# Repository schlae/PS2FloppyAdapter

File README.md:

# PS/2 Floppy Adapter

This PS/2 floppy adapter is designed to allow standard PC floppy drives to be
used in IBM PS/2 systems that have 40-pin edge connectors for their floppy
drive interfaces. This can be quite useful because many PS/2 floppy drives have failed due to leaking capacitors or mechanical problems, and can be difficult or impossible to repair.

Compatible models include

* IBM PS/2 Model 50 and 50Z
* IBM PS/2 Model 70

Here's what the adapter looks like when installed in a Model 50Z.

## Connector PC Board

There are several pieces to the design. First, there is a circuit board: the design files are here.

[Schematic](https://github.com/schlae/PS2FloppyAdapter/blob/master/PS2FloppyAdapter.pdf)

[Fab Files](https://github.com/schlae/PS2FloppyAdapter/blob/master/cam/PS2FloppyDaughterboardRevA.zip)

The bill of materials is as follows:

| Designator | Quantity | Description                  |
| ---------  | -------- | ---------------------------- |
|        J2  |        1 | 34-pin 0.1" breakaway header |
|      R1-R5 |        5 | 1K ohm resistors, 0603       |

Note that R1-R5 can be either 1% or 5% since the exact value is not critical.

J3 provides power to the PC floppy drive. One way to build it is to cut off
a 0.1" power header from an old PC power supply, Y splitter, or similar
adapter, and then solder the wires to the appropriate connections on the
adapter board. Black to ground, red to +5V, and yellow to +12V.

You'll also need a short length of 34-pin ribbon cable with a male IDC connector crimped onto each end. This connects the adapter board to the floppy drive.

## Mechanical Parts

Several parts mechanically adapt the standard PC floppy drive to fit in the
PS/2. Each of them can be printed on a commodity FDM 3D printer.

[Drive Sled](https://github.com/schlae/PS2FloppyAdapter/blob/master/mech/PS2_50_floppy_sled_15F7502.STL) - This is compatible with IBM FRU 15F7502. 

[Plugboard](https://github.com/schlae/PS2FloppyAdapter/blob/master/mech/PS2_50_floppy_plugboard.STL) - The plugboard sits between the floppy drive and the connector PC board, holding it at just the right angle.

[Eject button (Sony MPF920)](https://github.com/schlae/PS2FloppyAdapter/blob/master/mech/PS2_50_floppy_button_sony_mpf920.STL) - Eject button for the Sony MPF920 floppy drive

[Eject button (Teac FD235HF)](https://github.com/schlae/PS2FloppyAdapter/blob/master/mech/PS2_50_floppy_button_teac_fd235HF.STL) - Eject button for the Teac FD235HF floppy drive

The STL files are oriented in the optimal orientations for printing. The sled has some overhangs and will require supports to be added in order to print correctly.

* Two M3-0.5mm, 5mm long self tapping screws. These attach the PCB to the plugboard.

* Four M3-0.5mm, 10mm long machine screws. These attach the floppy drive to the sled.

## Assembly

Remove the old floppy drive bezel. The exact way to do this varies depending on the drive, but typically there are plastic tabs on the sides that clip into the drive. On some drives you may have to remove the metal lid to get at them.

Remove the old eject button from the floppy drive. The Sony drive button simply slides up. You might have to rock it back and forth a bit. The Teac drive button is harder to remove; if you get in with a dental pick or screwdriver, pull up the plastic catch and the button should slide straight out.

Install the new eject button just like you removed the old one but in reverse. If it refuses to go in, don't force it. There are some fairly detailed features that may require cleanup with a sharp knife in order for it to fit.

Before installing the drive on the sled, take the sled and heat the plastic locking tab in the front with a hair dryer or heat gun (low heat) and bend it down. It needs to bend down far enough to engage with a slot in the PS/2 chassis which locks it in place when it is installed.

Then, using the 10mm machine screws, install the drive on the sled. The floppy drive slot should face the same direction as the locking tab on the sled.

Install the PC board on the plastic plugboard using the two self-tapping screws. You can temporarily tape it in place to figure out how long the 34-pin IDC cable and the drive power cable need to be.

Now slide the assembly into your PS/2 computer and plug the PC board into the slot at the back of the drive bay. The plugboard should rest on the top of the floppy drive. Make a mark so you know exactly where it should go. Then remove the assembly and glue the plugboard to the top of the floppy drive, right where you placed your mark. You can try using double-sided tape, but 3M VHB (Very High Bond) is probably the most secure.

I've found that the drive LED lines up fairly well with the LED window on the stock PS/2 drive bezel (IBM FRU 15F7534).

There is a variant of the drive bezel, FRU 62X0362, which has the LED above the drive slot, which won't work. You'll need to run a wire and hot glue the LED on top of the floppy drive or print a replacement bezel (see below).

## Optional Parts

I've also made a 3D-printable model of the PS/2 Model 50/50Z drive bezel if you want to install this drive as a second floppy drive, or if your machine was missing it.

This part is tricky to print and requires support structures. It is printed on the side so that the front panel texture will look reasonable, and also so that the plastic locking tabs will be sturdy. Use pliers and side cutters to remove the support structure, and be sure to wear safety glasses!

## Archive

Here is the old version of the floppy adapter PC board. This can be used to electrically connect a floppy drive to the IBM 40-pin connector used on some additional models, such as the Model 60 and 80. There is no mechanical mounting design for these models yet.

[Fab Files](https://github.com/schlae/PS2FloppyAdapter/blob/master/cam/PS2FloppyAdapterRevA.zip)

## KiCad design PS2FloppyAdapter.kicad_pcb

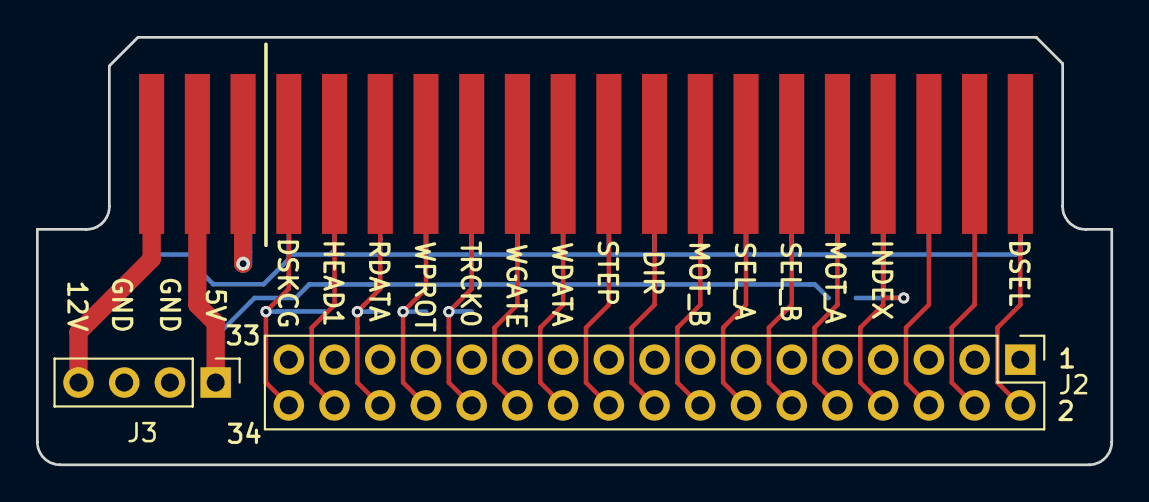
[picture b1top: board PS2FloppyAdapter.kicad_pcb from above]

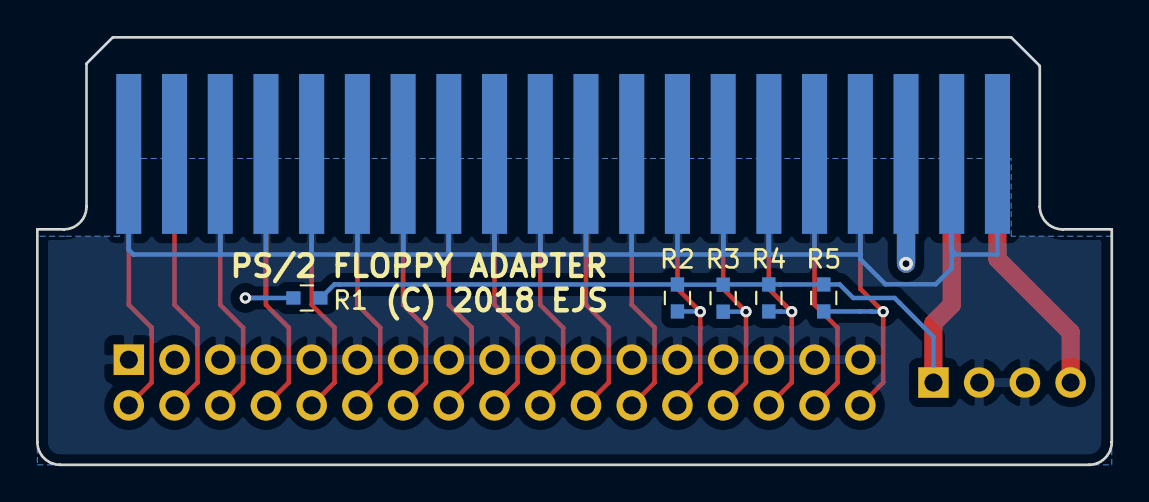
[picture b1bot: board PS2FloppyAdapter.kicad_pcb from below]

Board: 2 copper layers, 59.7 x 23.7 mm, 8 parts (5 on the bottom side), 21 nets.

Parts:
J1: Conn_02x20_Odd_Even; EDGE_FLOPPY40
J2: Conn_02x17_Odd_Even; Pin_Header_Straight_2x17_Pitch2.54mm
J3: Conn_01x04; Pin_Header_Straight_1x04_Pitch2.54mm
R1, R2, R3, R4, R5: 1K; RESC1608X55

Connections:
+5V: J1.38, J3.1, R1.1, R2.1, R3.1, R4.1, R5.1
+12V: J1.40, J3.4
/DIR: J1.18, J2.18
/DISKCHG: J1.34, J2.34, R5.2
/DSEL_A: J1.14, J2.14
/DSEL_B: J1.12, J2.12
/ENWRITE: J1.24, J2.24
/HDSEL: J1.2, J2.2
/HEAD1SEL: J1.32, J2.32
/INDEX: J1.8, J2.8, R1.2
/MOTEN_A: J1.10, J2.10
/MOTEN_B: J1.16, J2.16
/RDATA: J1.30, J2.30, R4.2
/RES1: J1.4, J2.4
/RES2: J1.6, J2.6
/STEP: J1.20, J2.20
/TRACK0: J1.26, J2.26, R2.2
/WDATA: J1.22, J2.22
/WPROT: J1.28, J2.28, R3.2
GND: J1.1, J1.5, J1.7, J1.9, J1.11, J1.13, J1.15, J1.17, J1.19, J1.21, J1.23, J1.25, J1.27, J1.29, J1.31, J1.33, J1.37, J1.39, J2.1, J2.5, J2.7, J2.9, J2.11, J2.13, J2.15, J2.17, J2.19, J2.21, J2.23, J2.25, J2.27, J2.29, J2.31, J2.33, J3.2, J3.3
unnamed: J1.35, J1.36

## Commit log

2020-03-21 Initial empty commit
2020-03-21 Initial version
2020-03-21 Fab out
2020-03-21 Add readme, update design files
2020-12-29 Added new board and mechanical parts

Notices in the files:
PS2FloppyAdapter.kicad_pcb:
Copyright (C) 2020 Eric Schlaepfer
License. See https://creativecommons.org/licenses/by-sa/4.0
This work is licensed under a Creative Commons Attribution-ShareAlike 4.0 International
(C) 2018 EJS
